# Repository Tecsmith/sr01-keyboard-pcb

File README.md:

# SR01-Keyboard-PCB

> **Note:** Rev "D" is a full redo in KiCAD, and has not been tested -- so, not suitable to build just yet.

## Intent

The 1-key<small><sup>1</sup></small> *"keyboard"* development platform.

## Features

This is not a "keyboard" per-se, it's a PCB that allows you you, with a **SeeedStudio** <a href="https://www.seeedstudio.com/XIAO-RP2040-v1-0-p-5026.html">XIAO RP2040</a> or <a href="https://www.seeedstudio.com/Seeed-XIAO-BLE-nRF52840-p-5201.html">XIAO nRF52840</a> module, to build:

* a 1-key MX-switch keyboard, with an RGB LED, <br>- *or* -
* a EC11 Rotary Encoder, with 4 RGB LED's, <br>- *or* -
* a 1-key HE *(Hall Effect)* switch keyboard, with a RGB LED, <br>- *or* -
* a 1-key EC *(Electrro Capacitance)* switch keyboard, <br> - *or* -
* a WHID solution, when *(the XIAO RP2040 is)* paired with a **SeeedStudio**:
  * <a href="https://www.seeedstudio.com/Seeed-Studio-XIAO-ESP32C6-p-5884.html">XIAO ESP32C6</a> module. [*Recommended*] , *- or -*
  * <a href="https://www.seeedstudio.com/Seeed-XIAO-ESP32C3-p-5431.html">XIAO ESP32C3</a> module, *- or -*
  * <a href="https://www.seeedstudio.com/XIAO-ESP32S3-p-5627.html">XIAO ESP32S3</a> module

for you to do some experimentations on.  These modules are intended to be breadboard mountable to that you can prototype your firmware and hardware ideas into verifiable solutions.

## Why?

When I built the SR61, one of the MicroMod modules I wanted to build for was the [SparkFun MicroMod ESP32 Processor](https://www.sparkfun.com/products/16781).. and for that I bought a [April Brother WHID Cactus](https://store.aprbrother.com/product/wifi-hid-injector) ... and then never got around to it.

The intent was to create a Wireless KB *(like a BT or 2.4GHz KB, but with WiFi)*, and also a whole bunch of additional features like a virtual web-KB, or the ability to configure the keys via it's own web interface.

This project is evolution of that idea.  *(The WHID Cactus is a ATmega 32u4 and ESP-12S combo. Old and limited.)*

And then the thought was: Why not also make it a Adafruit NeoKey Trinkey- / DigiSpark ATtiny85 USB key- ... -like one key?

Anyway ... what came out is a platform to build 1-key solutions for testing features, or just to have a quick volume control / sleep keep-alive / whatever you want to **play** with ... [*Software examples TBA*]

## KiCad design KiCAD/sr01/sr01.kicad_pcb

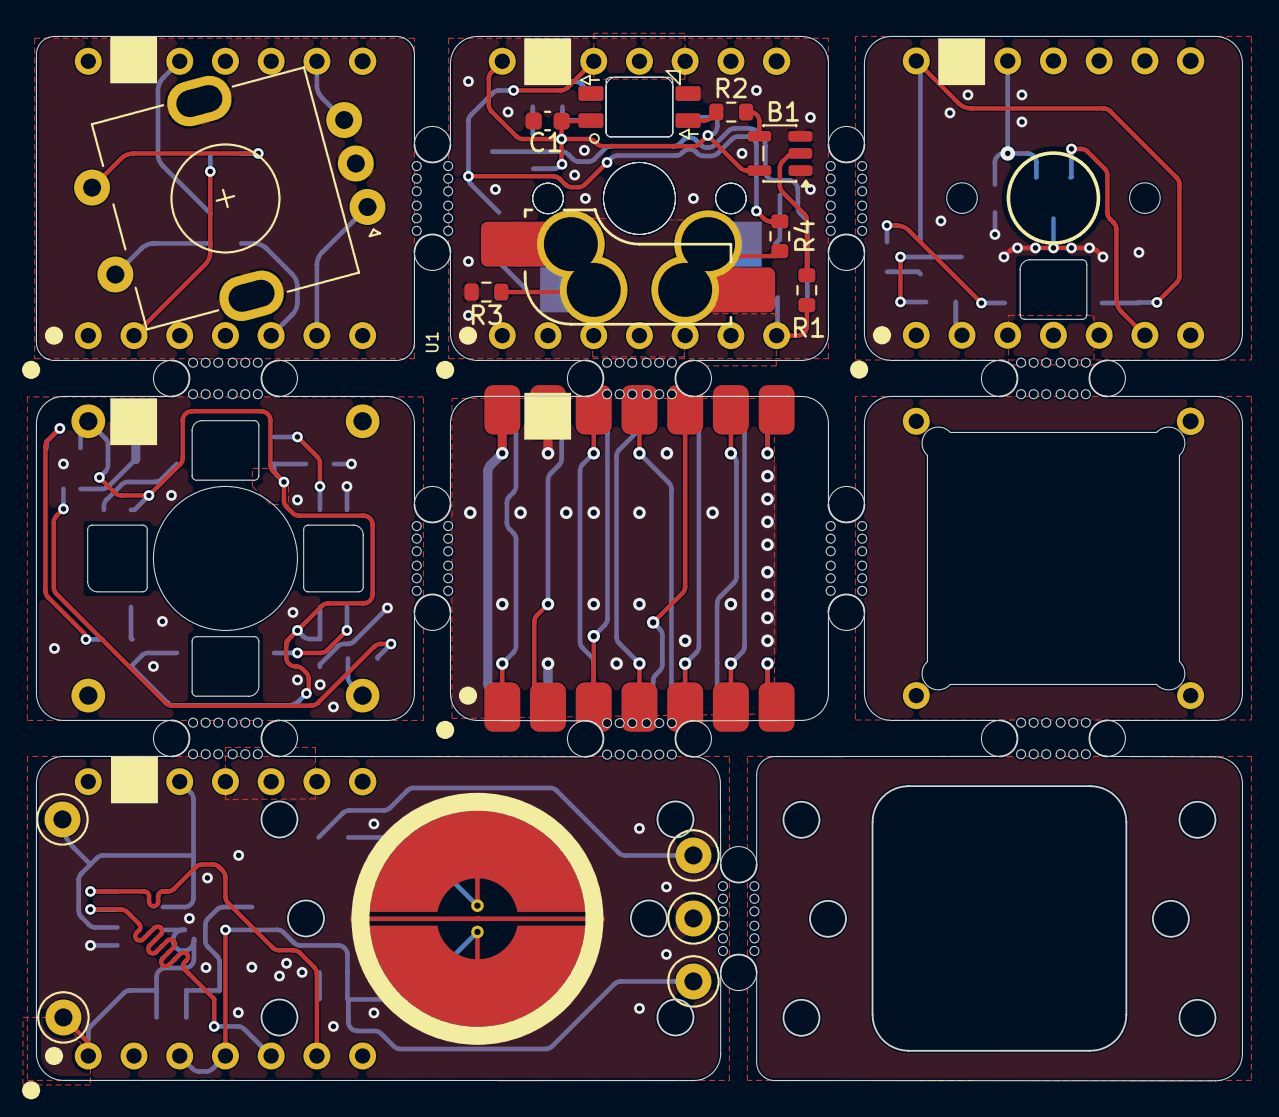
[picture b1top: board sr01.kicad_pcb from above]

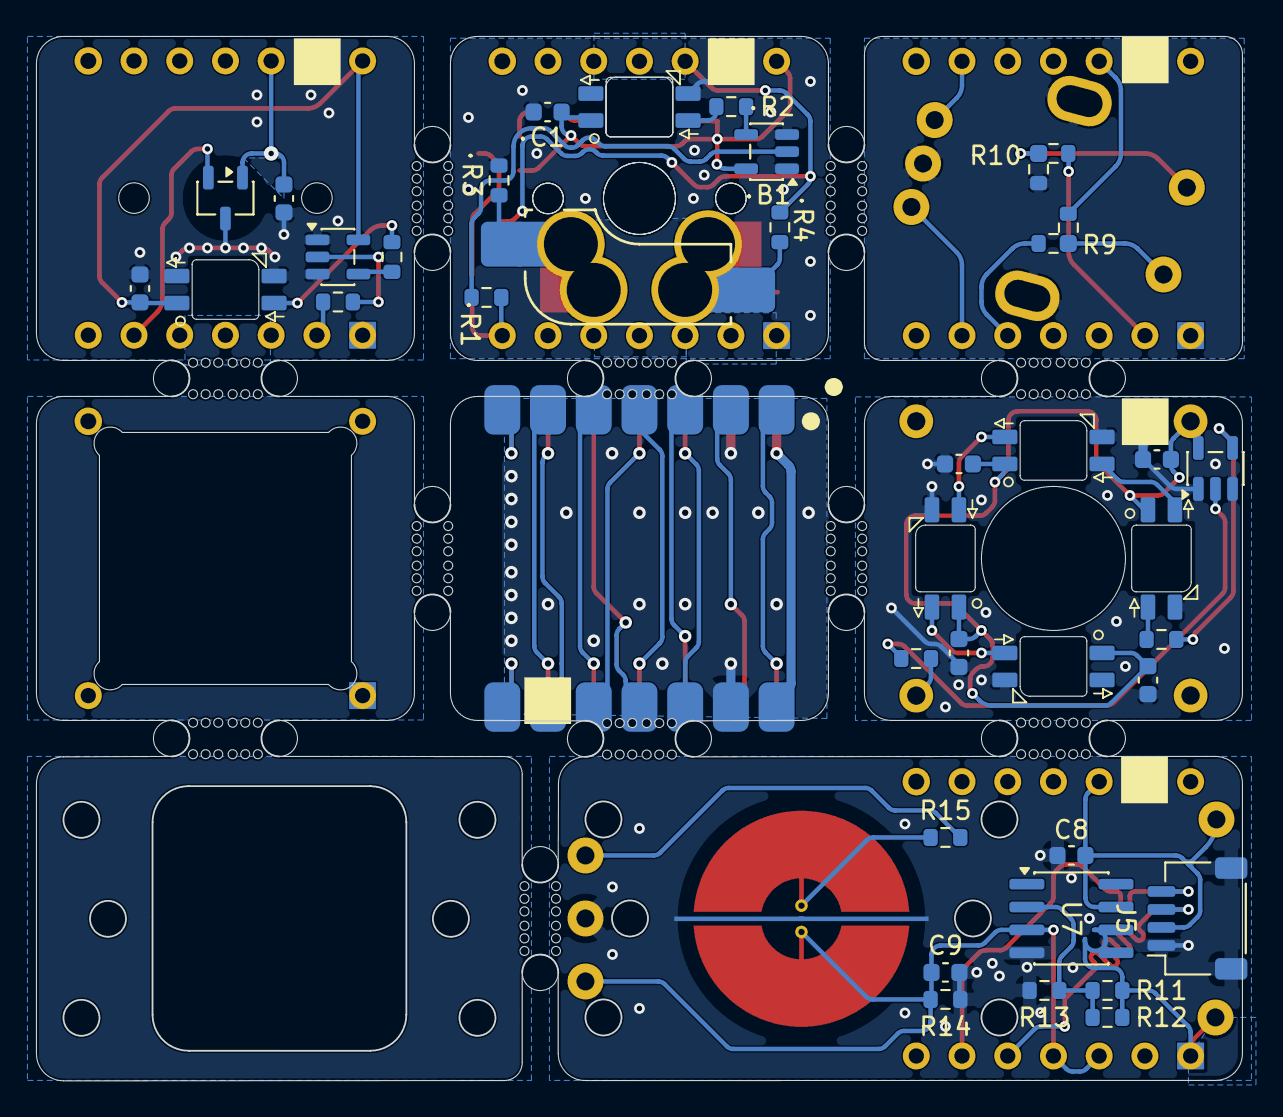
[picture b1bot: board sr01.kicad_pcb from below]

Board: 2 copper layers, 67.0 x 58.0 mm, 73 parts (39 on the bottom side), 48 nets.

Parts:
B1, B3, B4: SOT-23-5
C1, C2, C3, C4, C5, C6, C7, C8: 0.1uF; C_0603_1608Metric
C9: 220p; C_0603_1608Metric
J1: Conn_01x02; 1x02_P2.54mm
J2, J3, J4: Conn_01x01; 1x01_P2.54mm
J5: JST_SH_SM04B-SRSS-TB_1x04-1MP_P1.00mm_Horizontal
R1, R5, R7: 220R; R_0603_1608Metric
R2, R6, R8: 470R; R_0603_1608Metric
R3, R4, R12: DNP; R_0603_1608Metric
R9, R10: Jumper_R_0603_Short
R11, R14: 100K; R_0603_1608Metric
R13: 1K; R_0603_1608Metric
R15: 100R; R_0603_1608Metric
SW1, SW2: SW_MX_HotSwap
SW3: EC11; EC11-E
TP1, TP2, TP3, TP4, TP5: TestPoint_Keystone_5000-5004_Miniature
U1, U2, U3, U5: XIAO-Generic-DIP
U4: SW_DRV5056; SW_HE_DRV5056
U6: SW_EC_1U
U7: OPA350; SOIC-8_3.9x4.9mm_P1.27mm
U-PRIMARY-1: XIAO-RP2040; XIAO-Generic-SMD
U-SLAVE-1: XIAO-ESP32-C6; XIAO-Generic-SMD
W1, W3, W4, W5, W6, W7: SK6812MINI-E
mouse-bite-2mm-slot, mouse-bite-2mm-slot#2, mouse-bite-2mm-slot#3, mouse-bite-2mm-slot#4, mouse-bite-2mm-slot#5, mouse-bite-2mm-slot#6, mouse-bite-2mm-slot#7, mouse-bite-2mm-slot#8, mouse-bite-2mm-slot#9, mouse-bite-2mm-slot#10, mouse-bite-2mm-slot#11: VAL**; mouse-bite-2mm-slot
·B1: SOT-23-5
·C1: 0.1uF; C_0603_1608Metric
·R1: 220R; R_0603_1608Metric
·R2: 470R; R_0603_1608Metric
·R3, ·R4: DNP; R_0603_1608Metric
·W1: SK6812MINI-E

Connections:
+3V3: C6.2, C8.2, J5.2, R4.2, R9.3, TP5.1, U1.12 (3v3), U2.12 (3v3), U3.12 (3v3), U4.1 (VCC), U5.12 (3v3), U7.7 (V+), U-PRIMARY-1.12 (3V3), U-SLAVE-1.12 (3V3), ·R4.2
+5V: B1.5 (Vdd), B3.5 (Vdd), B4.5 (Vdd), C1.2, C2.2, C3.2, C4.2, C5.2, C7.2, J1.2, U1.14 (5V), U2.14 (5V), U3.14 (5V), U5.14 (5V), U-PRIMARY-1.14 (VBUS), U-SLAVE-1.14 (VBUS), W1.1 (Vdd), W3.1 (Vdd), W4.1 (Vdd), W5.1 (Vdd), W6.1 (Vdd), W7.1 (Vdd), ·B1.5 (Vdd), ·C1.2, ·W1.1 (Vdd)
ADC1: U3.6 (SCL), U4.2 (OUT)
ADC2: R11.1, R12.1, TP3.1, U5.1 (io0), U7.6 (Out)
COL: C9.2, R14.1, TP1.1, U5.3 (io2), U5.4 (io3), U6.1, U7.3 (In+)
ENC-A: SW3.A, U2.6 (SCL)
ENC-B: SW3.B, U2.9 (SCK)
GND: B1.1 (~OE), B1.3 (Gnd), B3.1 (~OE), B3.3 (Gnd), B4.1 (~OE), B4.3 (Gnd), C1.1, C2.1, C3.1, C4.1, C5.1, C6.1, C7.1, C8.1, C9.1, J1.1, J5.1, J5.MP, R3.1, R10.3, R13.2, R14.2, SW3.C, SW3.MP, TP4.1, U1.13 (GND), U2.13 (GND), U3.13 (GND), U4.3 (GND), U5.13 (GND), U6.3, U7.4 (V-), U-PRIMARY-1.13 (GND), U-SLAVE-1.13 (GND), W1.3 (Vss), W3.3 (Vss), W4.3 (Vss), W5.3 (Vss), W6.3 (Vss), W7.3 (Vss), ·B1.1 (~OE), ·B1.3 (Gnd), ·C1.1, ·R3.1, ·W1.3 (Vss)
IO0: U-PRIMARY-1.1 (GPIO26/ADC0/A0), U-SLAVE-1.1 (GPIO0/A0/D0)
IO1: U-PRIMARY-1.2 (GPIO27/ADC1/A1), U-SLAVE-1.2 (GPIO1/A1/D1)
IO2: U-PRIMARY-1.3 (GPIO28/ADC2/A2), U-SLAVE-1.3 (GPIO2/A2/D2)
IO2-1: R3.2, SW1.2, SW2.1, U1.3 (io2), ·R4.1
IO2-2: R10.2, U2.2 (io1)
IO3: U-PRIMARY-1.4 (GPIO29/ADC3/A3), U-SLAVE-1.4 (GPIO21/D3)
MISOMOSI: U-PRIMARY-1.10 (GPIO4/MISO), U-SLAVE-1.11 (GPIO18/D10/MOSI)
MOSIMISO: U-PRIMARY-1.11 (GPIO3/MOSI), U-SLAVE-1.10 (GPIO20/D9/MISO)
unnamed: B1.2 (A), R1.1
unnamed: B1.4 (Y), R2.2
unnamed: B3.2 (A), R5.1
unnamed: B3.4 (Y), R6.2
unnamed: B4.2 (A), R7.1
unnamed: B4.4 (Y), R8.2
unnamed: R9.1, SW3.D
unnamed: R10.1, SW3.E
unnamed: R15.2, U6.2
unnamed: R11.2, R12.2, R13.1, U7.2 (In-)
unnamed: R2.1, W1.4 (In)
unnamed: R6.1, W3.4 (In)
unnamed: W3.2 (Out), W4.4 (In)
unnamed: W4.2 (Out), W5.4 (In)
unnamed: W5.2 (Out), W6.4 (In)
unnamed: R8.1, W7.4 (In)
unnamed: ·B1.2 (A), ·R1.1
unnamed: ·B1.4 (Y), ·R2.2
unnamed: ·R2.1, ·W1.4 (In)
RGB-1: R1.2, U1.7 (TX), ·R1.2
RGB-2: J4.1 (Pin_1_1), R5.2
RGB-3: R7.2, U3.2 (io1)
ROW: R15.1, TP2.1
RXTX: U-PRIMARY-1.8 (GPIO1/RX), U-SLAVE-1.7 (GPIO16/D6/TX)
SCK: U-PRIMARY-1.9 (GPIO2/SCK), U-SLAVE-1.9 (GPIO19/D8/SCK)
SCL: U-PRIMARY-1.6 (GPIO7/SCL), U-SLAVE-1.6 (GPIO23/D5/SCL)
SCL2: J5.4, U5.6 (SCL)
SDA: U-PRIMARY-1.5 (GPIO6/SDA), U-SLAVE-1.5 (GPIO22/D4/SDA)
SDA2: J5.3, U5.5 (SDA)
SDA-1: R4.1, SW1.1, SW2.2, U1.5 (SDA), ·R3.2
SDA-2: R9.2, U2.5 (SDA)
TXRX: U-PRIMARY-1.7 (GPIO0/TX), U-SLAVE-1.8 (GPIO17/D7/RX)

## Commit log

2024-12-07 Rev C PCB
2026-04-29 Added KiCAD redo -- rev D
2026-05-02 add EC switch
